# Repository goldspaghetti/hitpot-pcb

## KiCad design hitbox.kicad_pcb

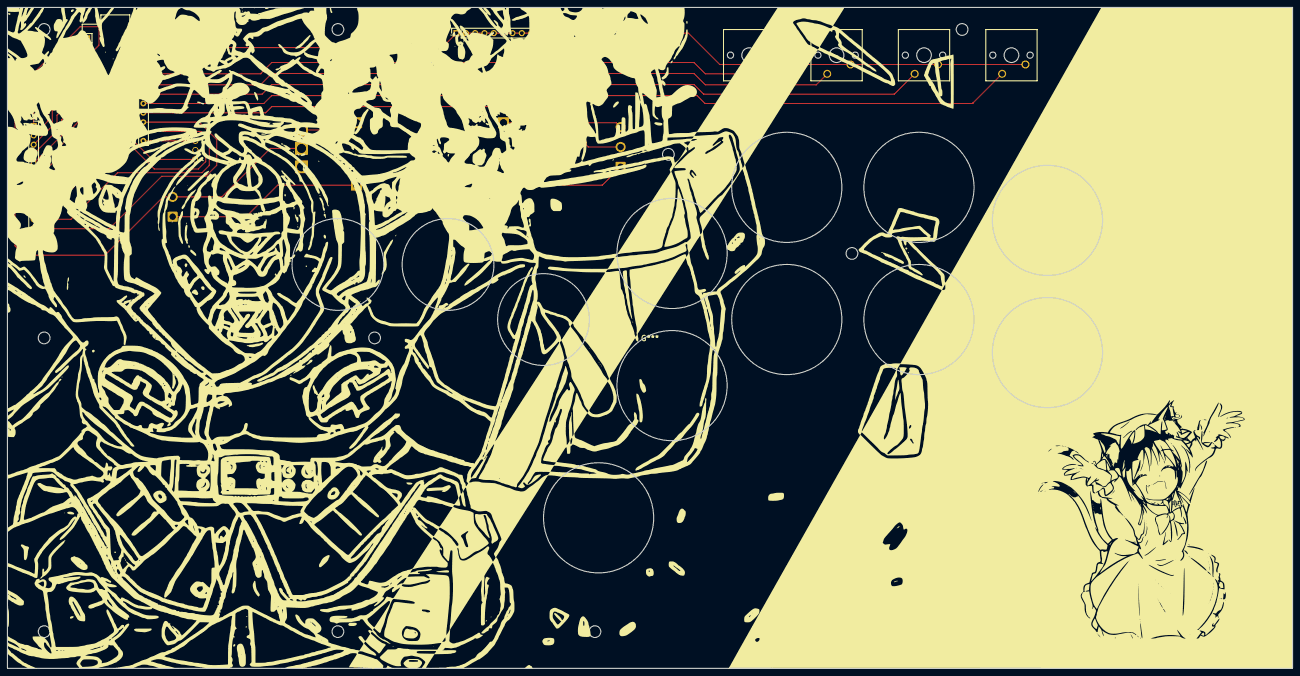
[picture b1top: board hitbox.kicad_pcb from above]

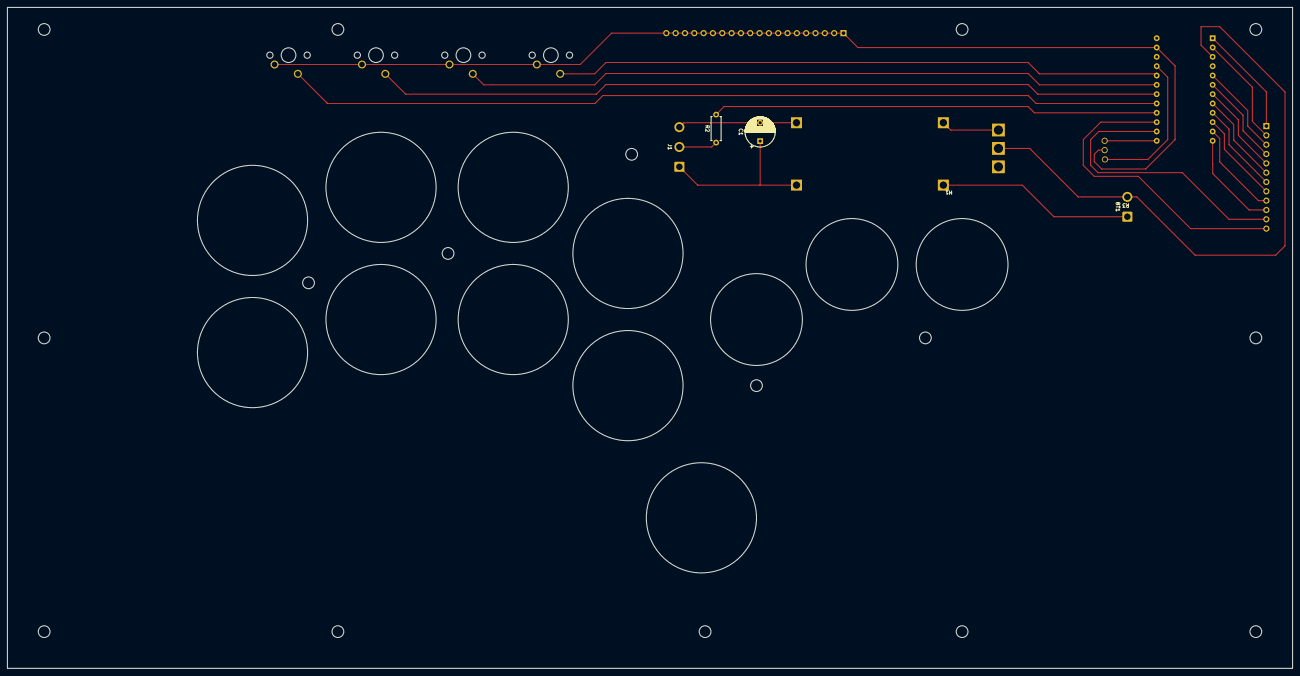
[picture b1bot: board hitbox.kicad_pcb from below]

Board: 2 copper layers, 350.0 x 180.0 mm, 13 parts (6 on the bottom side), 26 nets.

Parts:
BT1: Battery; SolderWire-1sqmm_1x02_P5.4mm_D1.4mm_OD2.7mm
C1: C; CP_Radial_D8.0mm_P5.00mm
H1: hw411
J1: Conn_01x03_Pin; SolderWire-1sqmm_1x03_P5.4mm_D1.4mm_OD2.7mm
J4: Conn_01x12_Socket; PinSocket_1x12_P2.54mm_Vertical
J5: Conn_01x20; PinSocket_1x20_P2.54mm_Vertical
R2: R; R_Axial_DIN0207_L6.3mm_D2.5mm_P7.62mm_Horizontal
R3: cw020
SW1, SW2, SW3, SW4: SW_DIP_x01; SW_Cherry_MX_1.25u_PCB
U1: Sparkfun_Pro_Micro

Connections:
1: R3.3 (IN), U1.13 (~D10/A10)
2: R2.2, U1.16 (D15)
17: J4.1, U1.1 (D1/TX)
18: J4.2, U1.2 (D0/RX)
19: J4.3, U1.5 (D2)
20: J4.4, U1.6 (~D3)
21: SW1.1, U1.17 (D18/A0)
22: SW2.1, U1.18 (D19/A1)
23: SW3.1, U1.19 (D20/A2)
24: SW4.1, U1.20 (D21/A3)
25: J4.9, U1.11 (D8/A8)
26: J4.10, U1.12 (~D9/A9)
27: J4.11, U1.14 (D16)
28: J4.12, U1.15 (D14)
29: J4.5, U1.7 (D4/A6)
30: J4.6, U1.8 (~D5)
31: J4.7, U1.9 (~D6/A7)
32: J4.8, U1.10 (D7)
GND1: J5.1, J5.2, J5.3, J5.4, J5.5, J5.6, J5.7, J5.8, J5.9, J5.10, J5.11, J5.12, J5.13, J5.14, J5.15, J5.16, J5.17, J5.18, J5.19, J5.20, R3.2 (GND), SW1.2, SW2.2, SW3.2, SW4.2, U1.23 (GND)
GND2: BT1.2 (-), R3.5 (COM), U1.3 (GND)
unnamed: BT1.1 (+), H1.1 (in+)
unnamed: H1.2 (in-), R3.6 (NO)
unnamed: C1.1, H1.3 (out+), J1.1
unnamed: C1.2, H1.4 (out-), J1.3
unnamed: J1.2, R2.1
VCC1: R3.1 (VCC), U1.21 (VCC)
